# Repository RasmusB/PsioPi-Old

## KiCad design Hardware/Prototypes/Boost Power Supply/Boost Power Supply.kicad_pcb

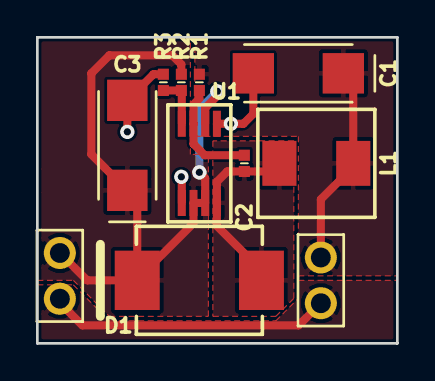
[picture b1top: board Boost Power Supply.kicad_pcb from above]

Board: 2 copper layers, 20.0 x 17.0 mm, 11 parts (0 on the bottom side), 6 nets.

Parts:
BT1: Battery; PIN_HEADER-1x2_RA
C1: 220uF; C-6032
C2: 4p7F; C-0402-1005
C3: 100uF; C-6032
D1: 3A; D-SMC
J1: 5V_OUT; PIN_HEADER-1x2_RA
L1: 4u7H; L-5mm6x5mm2
R1: 150k; R-0402-1005
R2: 300k; R-0402-1005
R3: 100k; R-0402-1005
U1: LM2623; S-PDSO-G8

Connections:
+5V: C3.1, D1.1, J1.2, R2.2, U1.2, U1.6, U1.7
+BATT: BT1.1, C1.1, L1.2, R1.2
GND: BT1.2, C1.2, C3.2, J1.1, R3.1, U1.1, U1.5
unnamed: C2.1, R1.1, U1.3
unnamed: C2.2, D1.2, L1.1, U1.8
unnamed: R2.1, R3.2, U1.4

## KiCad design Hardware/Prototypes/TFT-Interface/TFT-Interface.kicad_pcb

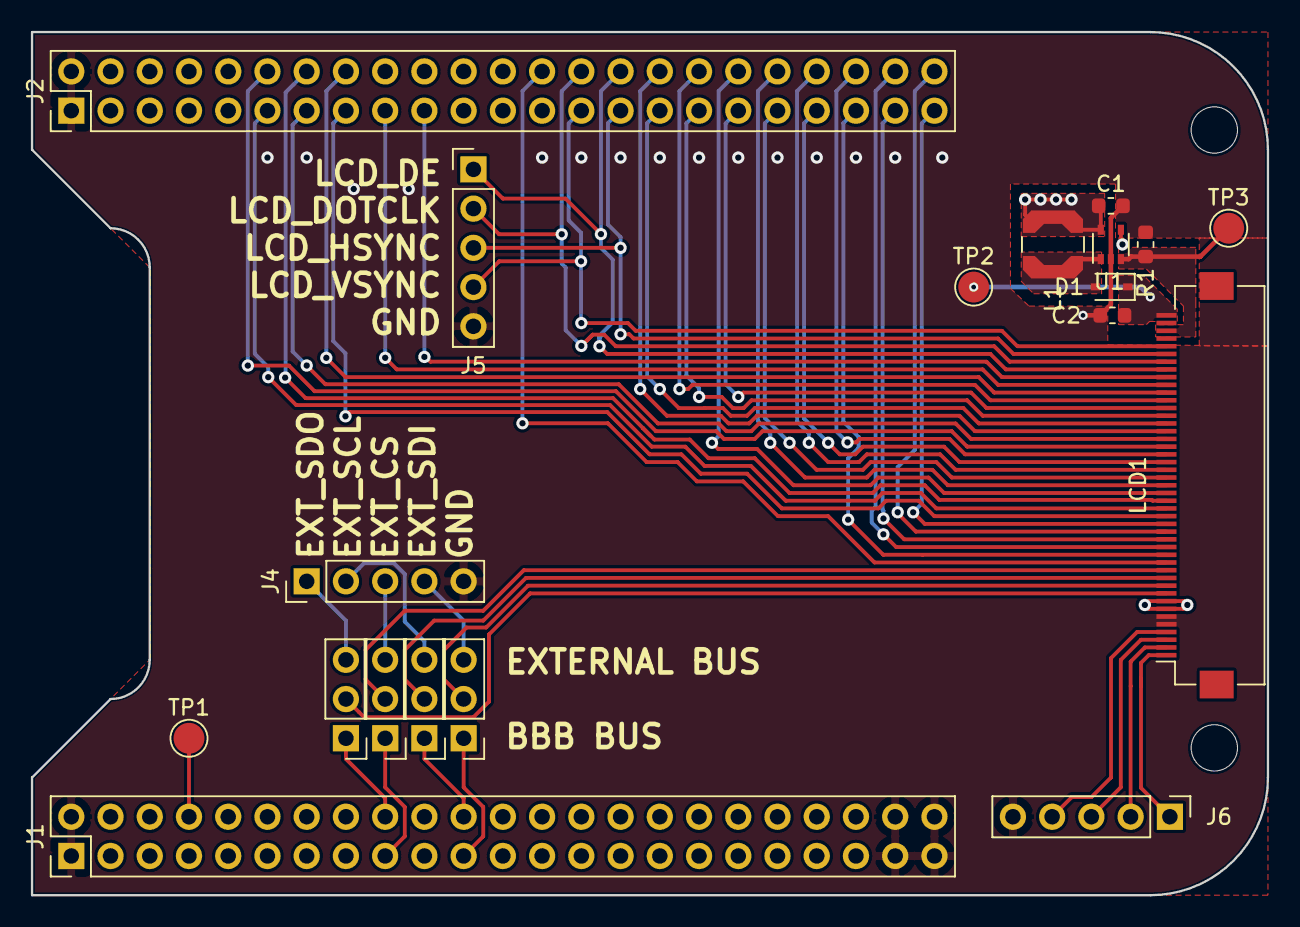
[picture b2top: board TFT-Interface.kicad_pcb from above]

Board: 4 copper layers, 80.0 x 55.9 mm, 19 parts (0 on the bottom side), 52 nets.

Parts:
C1: 4µ7 10v; C_0603_1608Metric
C2: 1µ 50v; C_0603_1608Metric
D1: NSR0240HT1G; D_SOD-323
J1, J2: BB_P8; PinHeader_2x23_P2.54mm_Vertical
J4: EXT_SPI; PinHeader_1x05_P2.54mm_Vertical
J5: LCD_CONTROL; PinHeader_1x05_P2.54mm_Vertical
J6: TOUCH_SIG; PinHeader_1x05_P2.54mm_Vertical
JUMPER1: SDO; PinHeader_1x03_P2.54mm_Vertical
JUMPER2: SCL; PinHeader_1x03_P2.54mm_Vertical
JUMPER3: CS; PinHeader_1x03_P2.54mm_Vertical
JUMPER4: SDI; PinHeader_1x03_P2.54mm_Vertical
L1: LPS4018-103MRB; L_Coilcraft_LPS4018
LCD1: E50RG84885LWAM520-CA; Hirose_FH12-45S-0.5SH_1x45-1MP_P0.50mm_Horizontal
R1: 5R1; R_0603_1608Metric
TP1: +5VP; TestPoint_Pad_D2.0mm
TP2: LED+; TestPoint_Pad_D2.0mm
TP3: LED-; TestPoint_Pad_D2.0mm
U1: TPS61169; SOT-353_SC-70-5

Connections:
+3V3: J1.3, J1.4, LCD1.7, LCD1.8
+5V: J1.5, J1.6
+5VP: C1.1, J1.7, J1.8, L1.2, TP1.1, U1.5
/BBB_CS: J1.17, JUMPER3.1
/BBB_SCL: J1.22, JUMPER2.1
/BBB_SDI: J1.21, JUMPER4.1
/BBB_SDO: J1.18, JUMPER1.1
/EXT_CS: J4.3, JUMPER3.3
/EXT_SCL: J4.2, JUMPER2.3
/EXT_SDI: J4.4, JUMPER4.3
/EXT_SDO: J4.1, JUMPER1.3
/LCD_B0: J2.19, LCD1.37
/LCD_B1: J2.17, LCD1.36
/LCD_B2: J2.16, LCD1.35
/LCD_B3: J2.34, LCD1.34
/LCD_B4: J2.35, LCD1.33
/LCD_B5: J2.33, LCD1.32
/LCD_B6: J2.31, LCD1.31
/LCD_B7: J2.32, LCD1.30
/LCD_CS: JUMPER3.2, LCD1.12
/LCD_DE: J2.30, J5.1, LCD1.38
/LCD_DOTCLK: J2.28, J5.2, LCD1.39
/LCD_G0: J2.13, LCD1.29
/LCD_G1: J2.12, LCD1.28
/LCD_G2: J2.42, LCD1.27
/LCD_G3: J2.39, LCD1.26
/LCD_G4: J2.40, LCD1.25
/LCD_G5: J2.37, LCD1.24
/LCD_G6: J2.38, LCD1.23
/LCD_G7: J2.36, LCD1.22
/LCD_HSYNC: J2.29, J5.3, LCD1.40
/LCD_R0: J2.14, LCD1.21
/LCD_R1: J2.11, LCD1.20
/LCD_R2: J2.15, LCD1.19
/LCD_R3: J2.45, LCD1.18
/LCD_R4: J2.46, LCD1.17
/LCD_R5: J2.43, LCD1.16
/LCD_R6: J2.44, LCD1.15
/LCD_R7: J2.41, LCD1.14
/LCD_RESET: J2.26, LCD1.13
/LCD_SCL: JUMPER2.2, LCD1.11
/LCD_SDI: JUMPER4.2, LCD1.10
/LCD_SDO: JUMPER1.2, LCD1.9
/LCD_VSYNC: J2.27, J5.4, LCD1.41
/LED_SW: D1.2, L1.1, U1.1
/TOUCH_XL: J6.3, LCD1.3
/TOUCH_XR: J6.1, LCD1.1
/TOUCH_YD: J6.2, LCD1.2
/TOUCH_YU: J6.4, LCD1.4
GND: C1.2, C2.2, J1.1, J1.2, J1.43, J1.44, J1.45, J1.46, J2.1, J2.2, J4.5, J5.5, J6.5, LCD1.5, LCD1.6, R1.2, U1.2
LED+: C2.1, D1.1, LCD1.45, TP2.1
LED-: LCD1.43, R1.1, TP3.1, U1.3
